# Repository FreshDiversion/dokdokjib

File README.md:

# dokdokjib
A DIY Home Automation System Using open source materials

The future is smart, the future is automated. The future belongs to the people.

Currently, as we are all aware, the majority of the innovations in technology that are available to the every-day individual are controlled by large corporations. The window through which the every-day person can conceive, develop, and produce their own technological innovations, on the scale of a full home automation system, is small.

This project concerned itself with the future of smart home automation(IOT), digital assistants(Siri, Google Home, Alexa), and the ever growing presence of voice recognition technologies(NLP). These concepts, and developing a user-friendly and accessible play that everyone can create and self educate in terms of developing their own technologies.

Our goal was to develop a system that was inexpensive and accessible to everyone. In addition, we found that many of our users would be individuals with little to no experience in technology. Our product had to be easy to install and customize for the user.

In keeping the cost to within an acceptable margin, we employed the concepts of up-cycling old technologies, creating within the boundaries of inexpensive microprocessors and microcomputers running open source software as well as basic code written by the team.

Exploring these concepts we examined the two sides of the home of the future. 
Automation: the sensing and collecting of data and Control: the user interface by which the resident home owner lives within a smart system.

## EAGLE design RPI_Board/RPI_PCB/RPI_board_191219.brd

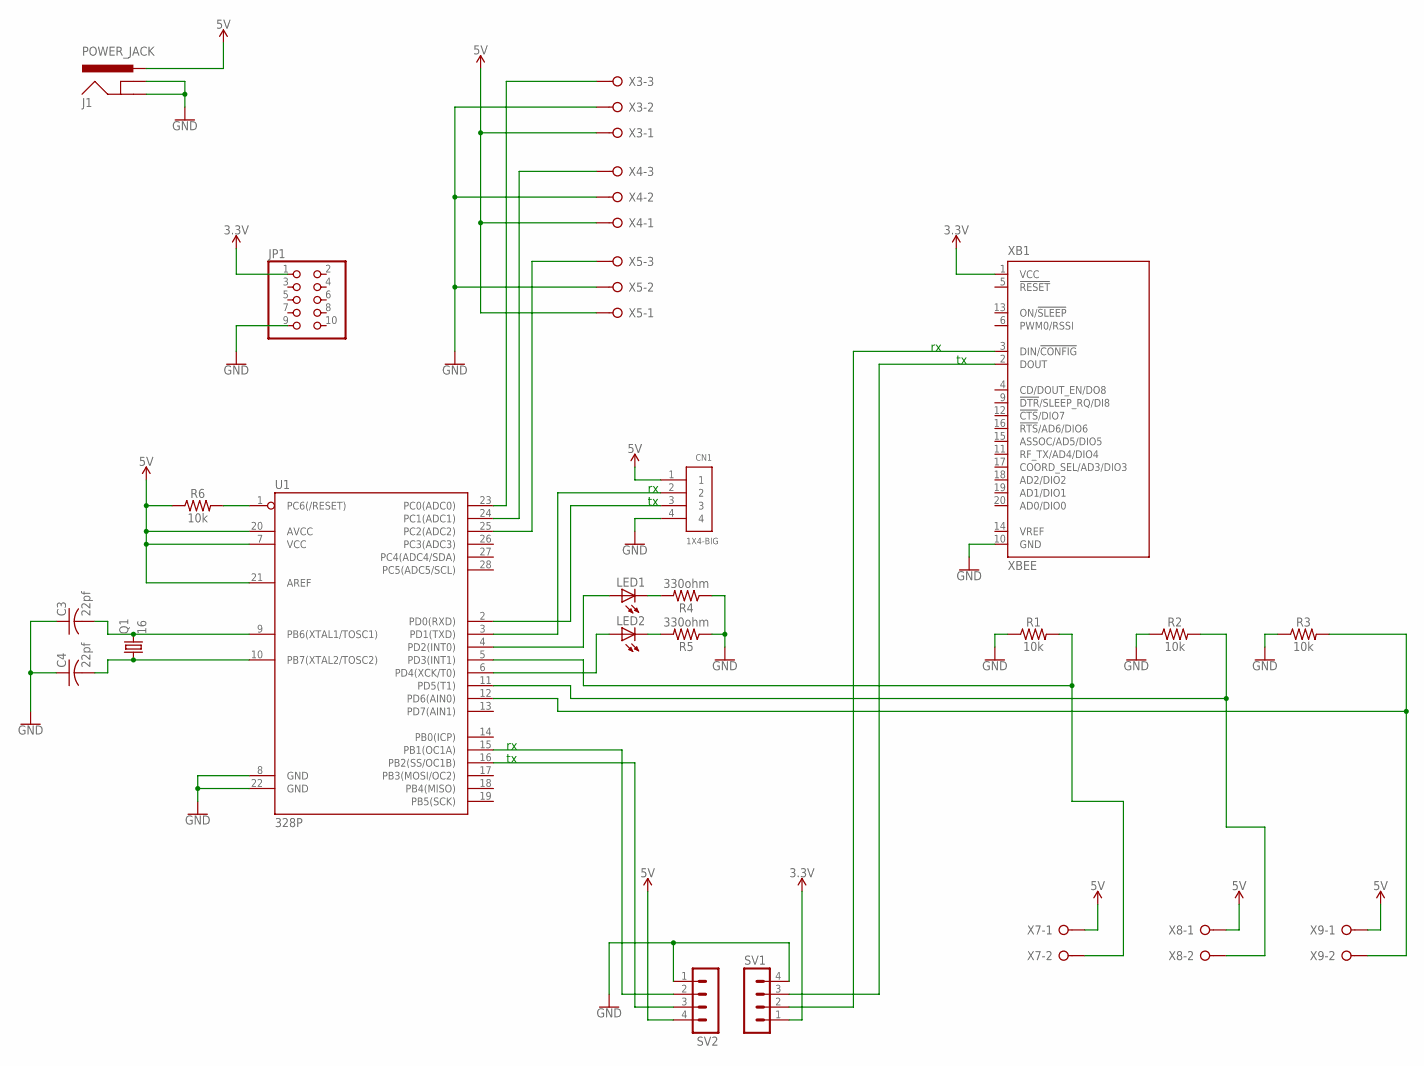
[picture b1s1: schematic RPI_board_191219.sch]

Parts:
C3, C4: 22pf; C050-025X075
CN1: 1X4-BIG; 1X04-BIG
J1: POWER_JACK; POWER_JACK_PTH
JP1: PINHD-2X5; 2X05
LED1, LED2: LED3MM
Q1: 16; HC49/S
R1, R2, R3, R6: 10k; AXIAL-0.3
R4, R5: 330ohm; AXIAL-0.3
SV1, SV2: MA04-1
U1: 328P; DIP28
X3, X4, X5: W237-3E
X7, X8, X9: W237-02P; W237-132
XB1: XBEE

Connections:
3.3V: JP1.1, SV1.1, XB1.1 (VCC)
5V: CN1.1, J1.PWR, R6.P$1 (1), SV2.4, U1.7 (VCC), U1.20 (AVCC), U1.21 (AREF), X3.1, X4.1, X5.1, X7.1, X8.1, X9.1
GND: C3.1, C4.1, CN1.4, J1.GND, J1.GNDBREAK, JP1.9, R1.P$1 (1), R2.P$1 (1), R3.P$1 (1), R4.P$1 (1), R5.P$1 (1), SV1.4, SV2.1, U1.8 (GND), U1.22 (GND), X3.2, X4.2, X5.2, XB1.10 (GND)
unnamed: CN1.3, U1.2 (PD0(RXD))
unnamed: CN1.2, U1.3 (PD1(TXD))
unnamed: U1.23 (PC0(ADC0)), X3.3
unnamed: U1.24 (PC1(ADC1)), X4.3
unnamed: U1.25 (PC2(ADC2)), X5.3
unnamed: LED1.A, U1.4 (PD2(INT0))
unnamed: LED2.A, U1.6 (PD4(XCK/T0))
unnamed: R1.P$2 (2), U1.5 (PD3(INT1)), X7.2
unnamed: LED2.K (C), R5.P$2 (2)
unnamed: LED1.K (C), R4.P$2 (2)
unnamed: C3.2, Q1.2, U1.9 (PB6(XTAL1/TOSC1))
unnamed: C4.2, Q1.1, U1.10 (PB7(XTAL2/TOSC2))
unnamed: R6.P$2 (2), U1.1 (PC6(/RESET))
unnamed: R3.P$2 (2), U1.12 (PD6(AIN0)), X9.2
unnamed: R2.P$2 (2), U1.11 (PD5(T1)), X8.2
unnamed: SV2.3, U1.16 (PB2(SS/OC1B))
unnamed: SV2.2, U1.15 (PB1(OC1A))
unnamed: SV1.2, XB1.3 (DIN/!CONFIG)
unnamed: SV1.3, XB1.2 (DOUT)

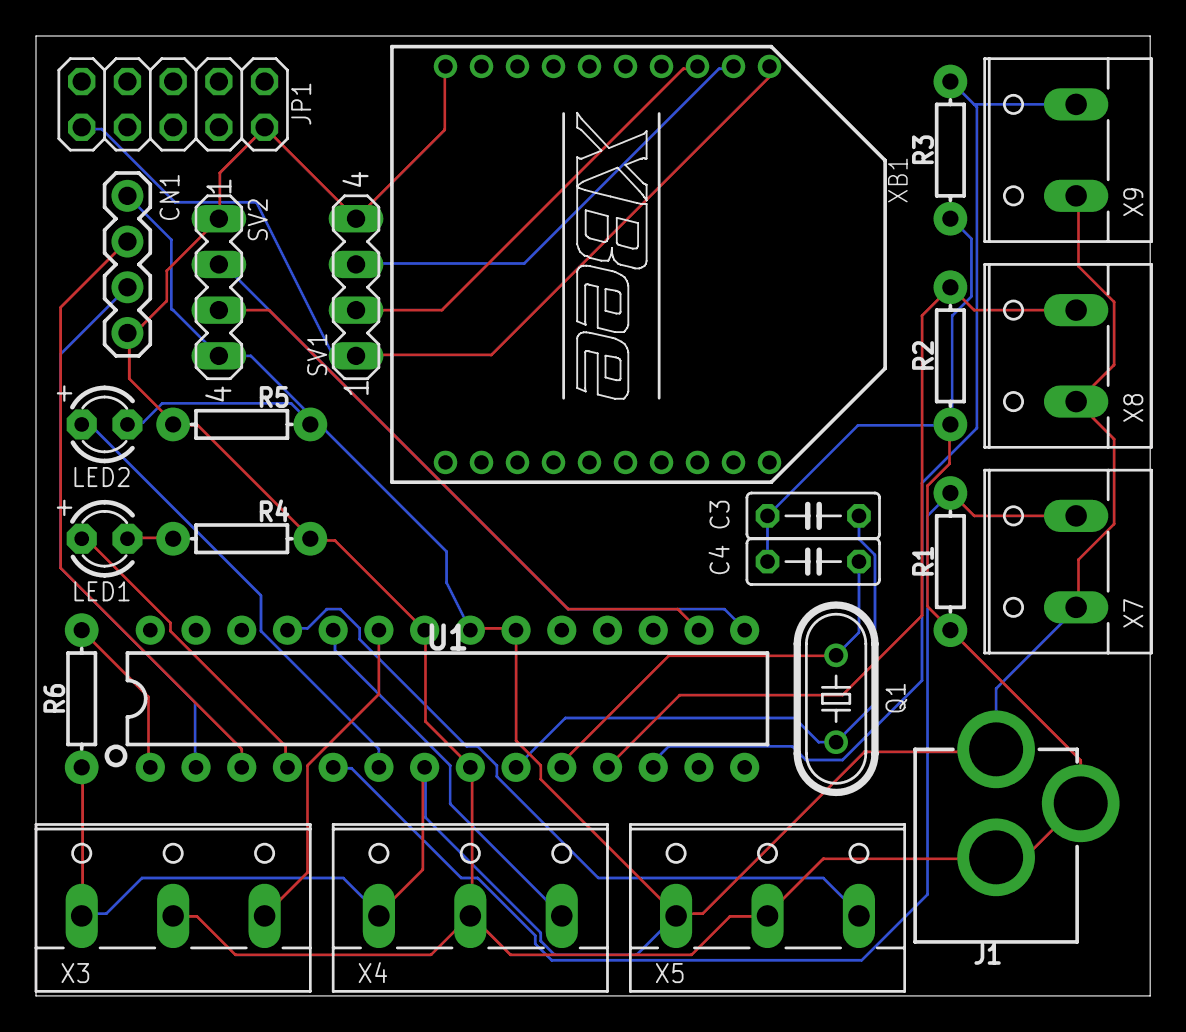
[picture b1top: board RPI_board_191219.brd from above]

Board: 2 copper layers, 61.9 x 53.3 mm, 24 parts (0 on the bottom side), 22 nets.

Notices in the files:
parts and their libraries:
SparkFun-Resistors: Licensing: Creative Commons ShareAlike 4.0 International - https://creativecommons.org/licenses/by-sa/4.0
